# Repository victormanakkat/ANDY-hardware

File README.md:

ANDY-hardware
=============

Repository for Andy's Hardware. All stls, SolidWorks files, KiCad files, and the like are included
here. Check out the main repository <a href="https://github.com/spadgenske/ANDY">here</a> and project 
page <a href="http://hackaday.io/project/1205">here</a>.

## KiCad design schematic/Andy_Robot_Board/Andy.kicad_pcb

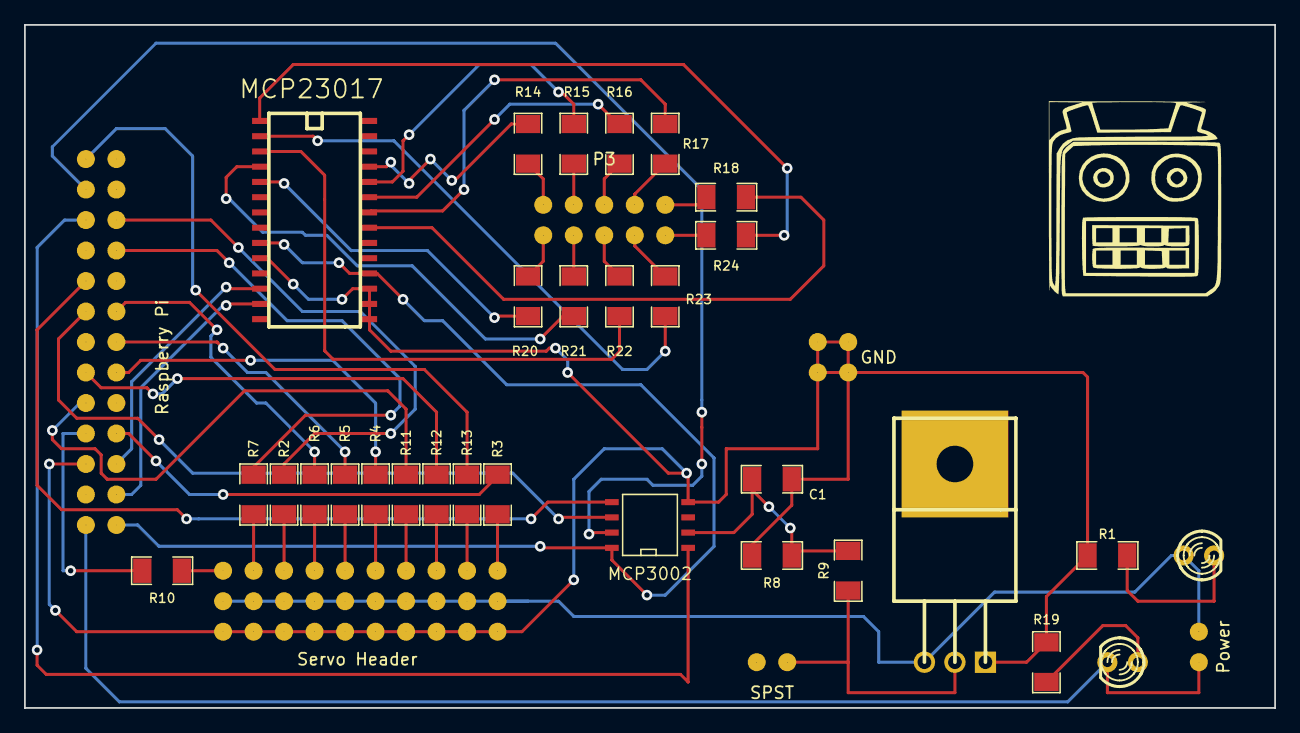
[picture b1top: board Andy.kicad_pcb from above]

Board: 2 copper layers, 104.1 x 56.9 mm, 45 parts (0 on the bottom side), 54 nets.

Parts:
C1: 0.1uF; SM1206
D1, D2: LED; LED-3MM
K1: Servo Header; ServoHeader
K2, K3, K4, K5, K6, K7, K8, K9, K10: Servo; ServoHeader
P1: Raspberry Pi; RaspberryPiHeader
P2: Power; jumper
P3: LED Strip; LED-Bar-Graph
P4: GND; GNDheader
R1, R14, R15, R16, R17, R18, R19, R20, R21, R22, R23, R24: 270; SM1206
R2, R3, R4, R5, R6, R7, R10, R11, R12, R13: 1K; SM1206
R8: 100K; SM1206
R9: 180K; SM1206
SW1: SPST; jumper
U1: MCP23017; SO28
U2: LM1084IT-5.0/NOPB; TO220
U3: MCP3002; SO8N

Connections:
GND: C1.2, K1.1, K2.1, K3.1, K4.1, K5.1, K6.1, K7.1, K8.1, K9.1, K10.1, P1.6, P4.1, P4.2, P4.3, P4.4, R1.2, R8.1, R19.2, U1.10, U1.15, U1.16, U1.17, U2.1, U3.4
unnamed: R22.2, U1.3
unnamed: R24.2, U1.1
unnamed: P3.10, R24.1
unnamed: P3.8, R23.1
unnamed: P3.6, R22.1
unnamed: P3.4, R21.1
unnamed: P3.2, R20.1
unnamed: R20.2, U1.5
unnamed: R21.2, U1.4
unnamed: R23.2, U1.2
unnamed: K10.3, R3.1
unnamed: K5.3, R5.1
unnamed: D2.x1, R19.1
unnamed: K4.3, R6.1
unnamed: P3.1, R14.2
unnamed: R14.1, U1.25
unnamed: R15.1, U1.24
unnamed: R16.1, U1.23
unnamed: R17.1, U1.22
unnamed: P3.3, R15.2
unnamed: P3.5, R16.2
unnamed: P3.7, R17.2
unnamed: P3.9, R18.2
unnamed: K2.3, R7.1
unnamed: D2.2, P1.2, P2.1
unnamed: P1.7, R3.2
unnamed: P1.19, R7.2
unnamed: P1.15, R6.2
unnamed: P1.13, R5.2
unnamed: P1.11, R4.2
unnamed: D1.2, R1.1
unnamed: K6.3, R4.1
unnamed: P1.26, R13.1
unnamed: K9.3, R13.2
unnamed: P1.12, R12.1
unnamed: P1.10, R11.1
unnamed: K1.3, R10.2
unnamed: P1.8, R10.1
unnamed: P1.21, R2.1
unnamed: K3.3, R2.2
unnamed: R18.1, U1.21
unnamed: K7.3, R11.2
unnamed: K8.3, R12.2
unnamed: P1.24, U3.7
unnamed: C1.1, R8.2, R9.1, U3.2
unnamed: P1.22, U3.1
unnamed: P1.18, U3.5
unnamed: P1.16, U3.6
unnamed: P1.3, U1.13
unnamed: P1.5, U1.12
unnamed: D1.1, K1.2, K2.2, K3.2, K4.2, K5.2, K6.2, K7.2, K8.2, K9.2, K10.2, P2.2, U2.2
unnamed: P1.1, U1.9, U1.18, U3.8
unnamed: R9.2, SW1.2, U2.3

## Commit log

2014-08-20 Added files
    Added current files from original repository
2014-08-21 Worked on PCB
2014-09-13 Added Andy 2.0 schematic
